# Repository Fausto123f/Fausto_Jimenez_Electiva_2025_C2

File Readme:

Proyectos y Documentacion de la materia Electiva para Mecatronicos
2023-0099 / Fausto Jimenez

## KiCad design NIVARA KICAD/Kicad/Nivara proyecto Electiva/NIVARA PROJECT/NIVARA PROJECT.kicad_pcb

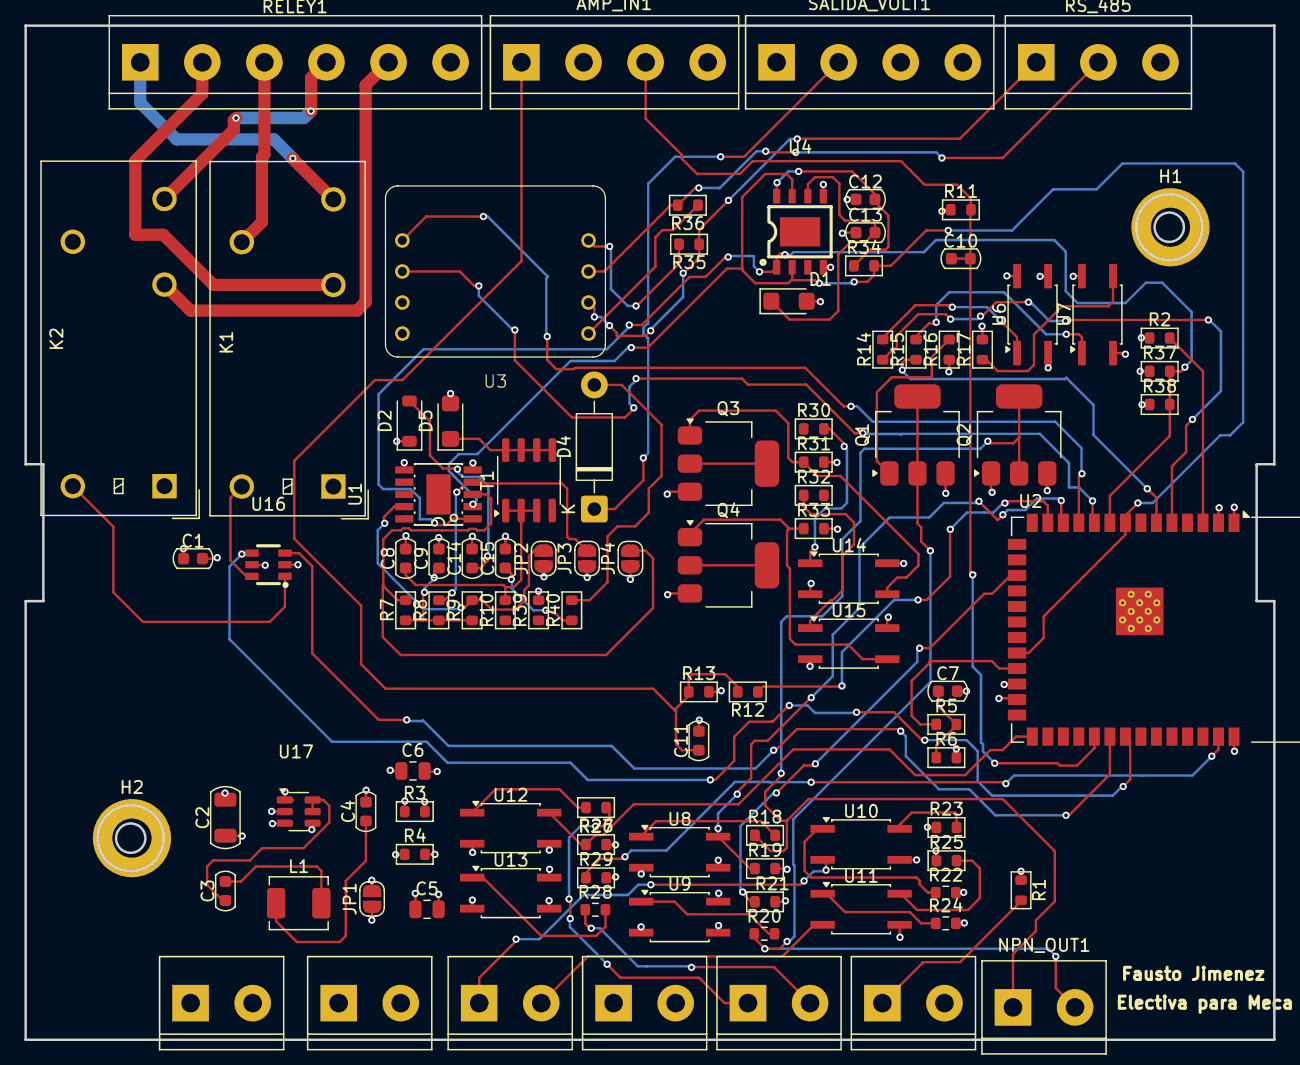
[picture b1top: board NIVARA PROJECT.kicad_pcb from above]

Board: 4 copper layers, 102.2 x 83.0 mm, 100 parts (0 on the bottom side), 72 nets.

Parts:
AMP_IN1: Screw_Terminal_01x04; TerminalBlock_bornier-4_P5.08mm
C1, C9: 1uf; C_0603_1608Metric
C2: 10uF; C_1206_3216Metric
C3, C4, C7, C10, C11, C13, C15: 100nF; C_0603_1608Metric
C5, C6: 22uF; C_0805_2012Metric
C8: 220nF; C_0603_1608Metric
C12, C14: 1uF; C_0603_1608Metric
D1, D5: SMF24A; D_SMF
D2: D_Zener; D_SOD-123
D4: 1N4007; D_DO-41_SOD81_P10.16mm_Horizontal
GRYND_IN1: Screw_Terminal_01x02; TerminalBlock_bornier-2_P5.08mm
H1, H2: MountingHole_M3_3.2mm_Pad; MountingHole_3.2mm_M3_Pad
JP1, JP2, JP3, JP4: SolderJumper_2_Open; SolderJumper-2_P1.3mm_Open_RoundedPad1.0x1.5mm
K1, K2: G2RL-1; Relay_SPDT_Omron_G2RL-1
L1: L_Iron; L_Chilisin_BMRA00040420
NPN_IN1: Screw_Terminal_01x02; TerminalBlock_bornier-2_P5.08mm
NPN_OUT1: Screw_Terminal_01x02; TerminalBlock_bornier-2_P5.08mm
PNP_IN1: Screw_Terminal_01x02; TerminalBlock_bornier-2_P5.08mm
PNP_OUT1: Screw_Terminal_01x02; TerminalBlock_bornier-2_P5.08mm
Q1, Q2, Q3, Q4: NCV8402xST; SOT-223
R1, R2, R7, R8, R9, R34: 10k; R_0603_1608Metric
R3, R4: 22K; R_0603_1608Metric
R5: 160k; R_0603_1608Metric
R6: 13k; R_0603_1608Metric
R10: 2.5k; R_0603_1608Metric
R11: 120; R_0603_1608Metric
R12: 51k; R_0603_1608Metric
R13: 16k; R_0603_1608Metric
R14, R15, R30, R32: 100; R_0603_1608Metric
R16, R17, R31, R33: 2.2k; R_0603_1608Metric
R18, R20, R22, R24, R26, R28: 910; R_0603_1608Metric
R19, R21, R23, R25, R27, R29: 412; R_0603_1608Metric
R35, R36: 47k; R_0603_1608Metric
R37, R38: 4.7k; R_0603_1608Metric
R39: 100k; R_0603_1608Metric
R40: 15; R_0603_1608Metric
RELEY1: Screw_Terminal_01x06; TerminalBlock_bornier-6_P5.08mm
RS_485: Screw_Terminal_01x03; TerminalBlock_bornier-3_P5.08mm
RUN/STOP1: Screw_Terminal_01x02; TerminalBlock_bornier-2_P5.08mm
SALIDA_VOLT1: Screw_Terminal_01x04; TerminalBlock_bornier-4_P5.08mm
T1: IRF9310TRPBF; SOIC-8_3.9x4.9mm_P1.27mm
U1: GP8303-TC50-EW; ESOP-10_L4.9-W3.9-P1.00-LS6.1-BL-EP
U2: ESP32-S3-WROOM-1
U3: 485
U4: GP8201S-TC50-EW; ESOP-8_L4.9-W3.9-P1.27-LS6.0-BL-EP
U6, U7, U14, U15: LTV-357T; SO-4_4.4x3.6mm_P2.54mm
U8, U9, U10, U11, U12, U13: LTV-357TB; SO-4_4.4x3.6mm_P2.54mm
U16: LK1802; SOT-23-6_L2.9-W1.6-P0.95-LS2.8-BR
U17: AP63200WU; TSOT-23-6
VCC_GND1: Screw_Terminal_01x02; TerminalBlock_bornier-2_P5.08mm

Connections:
+3.3V: C1.1, D2.1 (K), JP1.2 (B), K1.A1, K2.A1, R1.1, R2.1, R19.2, R21.2, R22.2, R23.1, R24.2, R25.1, R27.2, R29.2, R37.1, R38.1, U1.5 (VCC), U2.2 (3V3), U2.24 (IO47), U2.25 (IO48), U3.1 (vcc), U4.4 (VCC), U6.4, U7.4, U9.4, U13.4, U14.4, U15.4, U16.5 (COM)
/BOARD_NIVARA/10v In/10V_AIN: R12.1, U2.13 (USB_D-)
/BOARD_NIVARA/32vIn/A032_ADC2: C7.1, R5.2, R6.1
/BOARD_NIVARA/32vIn/A032_IN1: R5.1, U2.23 (IO21)
/BOARD_NIVARA/A010_IN_1: AMP_IN1.1, C11.1, R12.2, R13.1
/BOARD_NIVARA/A420_IN1: AMP_IN1.3, C10.1, C10.2, R11.2, U2.31 (IO38)
/BOARD_NIVARA/AOUT_010_: D4.1 (K), SALIDA_VOLT1.2
/BOARD_NIVARA/DA_IN_1: GRYND_IN1.1, U10.2
/BOARD_NIVARA/DA_IN_2: GRYND_IN1.2, U11.2
/BOARD_NIVARA/DRIVER-485/UART_IN: U2.10 (IO17), U3.3 (txd)
/BOARD_NIVARA/DRIVER-485/UART_OUT: U2.11 (IO18), U3.4 (rxd)
/BOARD_NIVARA/NPN_IN/NPN_OUT_C: R19.1, U2.12 (IO8), U8.4
/BOARD_NIVARA/NPN_IN/NPN_OUT_D: R21.1, U2.17 (IO9)
/BOARD_NIVARA/NPN_OUT/NPN_OUT_A: R15.1, U2.6 (IO6)
/BOARD_NIVARA/NPN_OUT/NPN_OUT_B: R14.1, U2.5 (IO5)
/BOARD_NIVARA/NPN_OUT_1: NPN_OUT1.1, Q2.2 (D), Q2.4 (D), R18.1
/BOARD_NIVARA/NPN_OUT_2: NPN_OUT1.2, Q1.2 (D), Q1.4 (D), R20.1
/BOARD_NIVARA/PNP_IN/NPN_OUT_C: R27.1, U2.27 (IO0), U12.4
/BOARD_NIVARA/PNP_IN/NPN_OUT_D: R29.1, U2.39 (IO1)
/BOARD_NIVARA/PNP_OUT/PNP_DOUT_1: Q3.2 (D), Q3.4 (D)
/BOARD_NIVARA/PNP_OUT/PNP_DOUT_2: Q4.2 (D), Q4.4 (D)
/BOARD_NIVARA/PNP_OUT_1: PNP_OUT1.1, R26.1
/BOARD_NIVARA/PNP_OUT_2: PNP_OUT1.2, R28.1
/BOARD_NIVARA/POWERSUPPLY/vout: C4.1, L1.1
/BOARD_NIVARA/RLY1_C: K1.11, RELEY1.3
/BOARD_NIVARA/RLY1_NC: K1.12, RELEY1.2
/BOARD_NIVARA/RLY1_NO: K1.14, RELEY1.1
/BOARD_NIVARA/RLY2_NC: K2.12, RELEY1.5
/BOARD_NIVARA/RLY2_NO: K2.14, RELEY1.4
/BOARD_NIVARA/RS_485_A: R35.1, RS_485.1, U3.9 (A)
/BOARD_NIVARA/RS_485_B: R36.2, RS_485.2, U3.8 (B)
/BOARD_NIVARA/RUN/STOP: R1.2, RUN/STOP1.1
/BOARD_NIVARA/VOLTAGE_OUT/SCLK: R37.2, R38.2, U1.1 (SLCK), U2.9 (IO16), U4.1 (SCLK)
/BOARD_NIVARA/VOLTAGE_OUT/SDA: R34.2, U1.2 (SDA), U2.8 (IO15), U2.22 (IO14), U4.2 (SDA), U4.7 (SEL)
/BOARD_NIVARA/VOLTAGE_OUT_PUT: C13.2, D1.1 (A1), U4.6 (VOUT)
/BOARD_NIVARA/relay/RL1_EN: U2.32 (IO39), U16.3 (1B)
/BOARD_NIVARA/relay/RL2_EN: U2.33 (IO40), U16.4 (2B)
GND: AMP_IN1.4, C1.2, C2.2, C4.2, C5.1, C5.2, C6.1, C6.2, C7.2, C8.2, C9.2, C11.2, C12.1, C13.1, C14.2, C15.2, D1.2 (A2), D5.2 (A2), H1.1, H2.1, JP1.1 (A), JP2.1 (A), JP3.1 (A), JP4.1 (A), Q1.3 (S), Q2.1 (G), Q2.3 (S), Q3.3 (S), Q4.3 (S), R3.1, R3.2, R4.1, R4.2, R6.2, R11.1, R13.2, R16.1, R17.2, R31.2, R33.2, R39.2, RS_485.3, RUN/STOP1.2, SALIDA_VOLT1.4, U1.6 (GND), U2.1 (GND), U2.40 (GND), U2.41 (GND), U3.2 (gnd), U4.5 (GND), U6.2, U6.3, U7.2, U8.2, U8.3, U9.2, U9.3, U10.3, U11.3, U12.2, U12.3, U13.2, U13.3, U14.2, U15.2, U16.2 (E), U17.1 (FB), U17.4 (GND), VCC_GND1.2
unnamed: C3.2, L1.2
unnamed: C8.1, R10.2, T1.1, T1.2, T1.3
unnamed: C14.1, D2.2 (A), R39.1, T1.4
unnamed: D4.2 (A), R40.2
unnamed: C15.1, D5.1 (A1), R40.1, T1.5, T1.6, T1.7, T1.8
unnamed: JP2.2 (B), R9.2, U1.9 (A2)
unnamed: JP3.2 (B), R8.2, U1.4 (A1)
unnamed: JP4.2 (B), R7.2, U1.3 (A0)
unnamed: Q1.1 (G), R16.2
unnamed: Q3.1 (G), R31.1, U14.3
unnamed: Q4.1 (G), R33.1, U15.3
unnamed: R14.2, U6.1
unnamed: R15.2, U7.1
unnamed: R17.1, U7.3
unnamed: R18.2, U8.1
unnamed: R20.2, U9.1
unnamed: R22.1, U10.1
unnamed: R23.2, U10.4
unnamed: R24.1, U11.1
unnamed: R25.2, U11.4
unnamed: R26.2, U12.1
unnamed: R28.2, U13.1
unnamed: R30.2, U14.1
unnamed: R32.1, U15.1
unnamed: R10.1, U1.7 (SET)
unnamed: C9.1, R7.1, R8.1, R9.1, U1.10 (V5V)
unnamed: R2.2, U2.3 (EN)
unnamed: R35.2, U3.7 (V0)
unnamed: R36.1, U3.10 (rgnd)
unnamed: C12.2, R34.1, U4.8 (V5V)
unnamed: K2.A2, U16.1 (1C)
unnamed: K1.A2, U16.6 (2C)
unnamed: C3.1, U17.5 (SW), U17.6 (BST)
VCC: C2.1, U17.2 (EN), U17.3 (IN), VCC_GND1.1

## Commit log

2025-06-04 Create Tarea 2 Diseño carcasa
2025-06-04 Create piezas
2025-06-04 Rename carcasa tarea 2/free cad/piezas to carcasa tarea 2/free cad/solid edge/piezas
2025-06-04 Create Carcasa
2025-06-04 Create ada
2025-06-04 Create a
2025-06-06 Garabato
2025-06-14 Create ,
2025-06-14 Create Tareas escritas
2025-06-20 Create p
2025-07-14 Create 1.
2025-07-14 Create p2
2025-07-14 Create p1
2025-07-15 Rename tarea 5 investigacion.pdf to tarea 5 MBSE
2025-07-15 Create Investigacion
